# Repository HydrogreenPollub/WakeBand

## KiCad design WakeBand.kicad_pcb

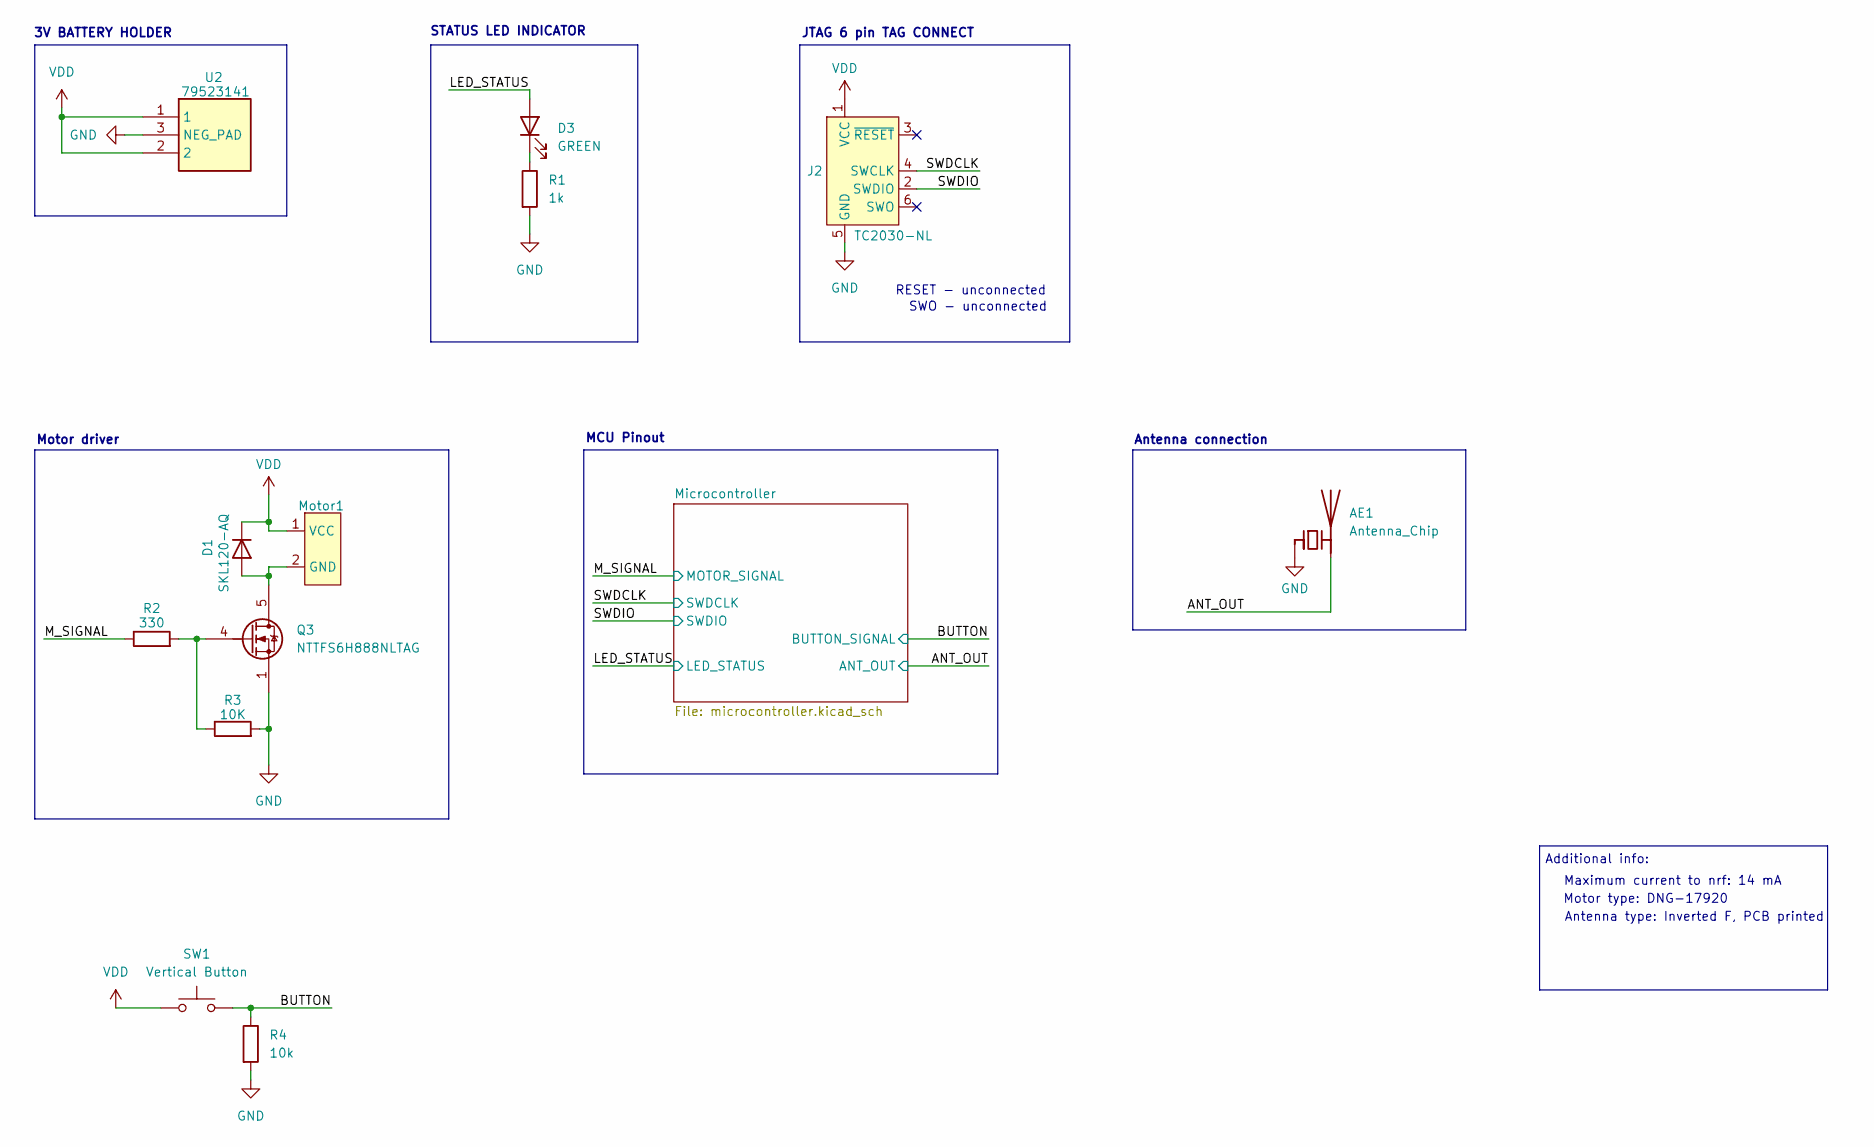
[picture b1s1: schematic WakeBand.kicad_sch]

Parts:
AE1: Antenna_Chip; ESPRESSIF_ESP32_MIFA_2.4GHz_Right
D1: SKL120-AQ; SODFL3718X170N
D3: GREEN; LED_1206_3216Metric
J2: TC2030-NL; Tag-Connect_TC2030-IDC-NL_2x03_P1.27mm_Vertical
Motor1: C_1206_3216Metric_Pad1.33x1.80mm_HandSolder
Q3: NTTFS6H888NLTAG; NRVTS560ETFS; Manufacturer_Part_Number NTTFS6H888NLTAG
R1: 1k; C_0402_1005Metric
R2: 330; C_0402_1005Metric
R3: 10K; C_0402_1005Metric
R4: 10k; R_0402_1005Metric
SW1: Vertical Button; Pushbutton from ST
U2: 79523141; Mouser Part Number 710-79523141

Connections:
/ANT_OUT: AE1.2 (PCB_Trace); also elsewhere on the board
/BUTTON: R4.1, SW1.2; also elsewhere on the board
/LED_STATUS: D3.2 (A); also elsewhere on the board
/M_SIGNAL: R2.1; also elsewhere on the board
/SWDCLK: J2.4 (SWCLK); also elsewhere on the board
/SWDIO: J2.2 (SWDIO); also elsewhere on the board
GND: AE1.1 (FEED), J2.5 (GND), Q3.1, R1.2, R3.2, R4.2, U2.3 (NEG_PAD); also elsewhere on the board
unnamed 14: D1.2 (A), Motor1.2 (GND), Q3.5; also elsewhere on the board
unnamed: D3.1 (K), R1.1
unnamed: Q3.4, R2.2, R3.1
VDD: D1.1 (K), J2.1 (VCC), Motor1.1 (VCC), SW1.1, U2.1, U2.2; also elsewhere on the board

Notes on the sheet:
Maximum current to nrf: 14 mA
Additional info:
MCU Pinout
JTAG 6 pin TAG CONNECT
SWO - unconnected
Motor type: DNG-17920
Antenna connection
STATUS LED INDICATOR
3V BATTERY HOLDER
RESET - unconnected
Motor driver
Antenna type: Inverted F, PCB printed

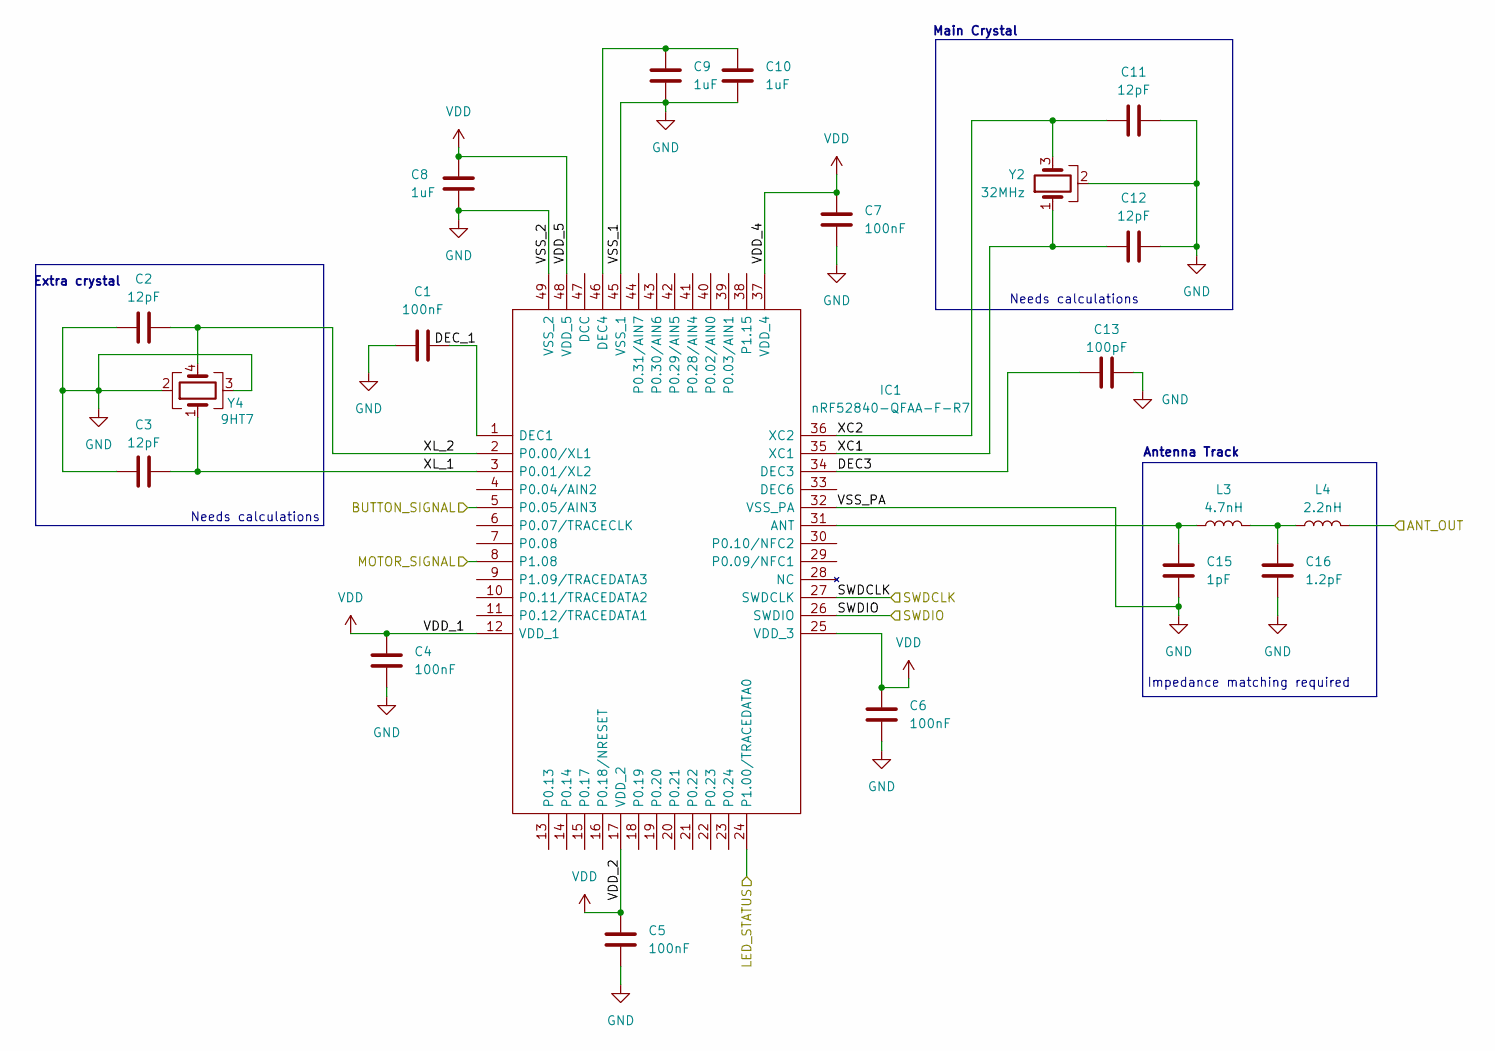
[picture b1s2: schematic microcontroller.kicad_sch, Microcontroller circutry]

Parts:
C1, C4, C5, C6, C7: 100nF; C_0402_1005Metric
C2, C3, C11, C12: 12pF; C_0402_1005Metric
C8, C9, C10: 1uF; C_0402_1005Metric
C13: 100pF; C_0402_1005Metric
C15: 1pF; C_0402_1005Metric
C16: 1.2pF; C_0402_1005Metric
IC1: nRF52840-QFAA-F-R7; QFN40P600X600X95-49N-D; Mouser Part Number 949-NRF52840QFAAF-R7
L3: 4.7nH; C_0402_1005Metric
L4: 2.2nH; C_0402_1005Metric
Y2: 32MHz; ECS320847BJTMTR
Y4: 9HT7; 9HT732768KDZFT

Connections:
/ANT_OUT: L4.2; also elsewhere on the board
/BUTTON: IC1.5 (P0.05/AIN3); also elsewhere on the board
/LED_STATUS: IC1.24 (P1.00/TRACEDATA0); also elsewhere on the board
/M_SIGNAL: IC1.8 (P1.08); also elsewhere on the board
/Microcontroller/DEC3: C13.1, IC1.34 (DEC3)
/Microcontroller/DEC_1: C1.2, IC1.1 (DEC1)
/Microcontroller/XC1: C12.1, IC1.35 (XC1), Y2.1
/Microcontroller/XC2: C11.1, IC1.36 (XC2), Y2.3
/Microcontroller/XL_1: C3.2, IC1.3 (P0.01/XL2), Y4.1
/Microcontroller/XL_2: C2.2, IC1.2 (P0.00/XL1), Y4.4
/SWDCLK: IC1.27 (SWDCLK); also elsewhere on the board
/SWDIO: IC1.26 (SWDIO); also elsewhere on the board
GND: C1.1, C2.1, C3.1, C4.2, C5.2, C6.2, C7.1, C8.1, C9.1, C10.1, C11.2, C12.2, C13.2, C15.2, C16.2, IC1.32 (VSS_PA), IC1.45 (VSS_1), IC1.49 (VSS_2), Y2.2, Y4.2, Y4.3; also elsewhere on the board
unnamed: C16.1, L3.2, L4.1
unnamed: C15.1, IC1.31 (ANT), L3.1
unnamed: C9.2, C10.2, IC1.46 (DEC4)
VDD: C4.1, C5.1, C6.1, C7.2, C8.2, IC1.12 (VDD_1), IC1.17 (VDD_2), IC1.25 (VDD_3), IC1.37 (VDD_4), IC1.48 (VDD_5); also elsewhere on the board

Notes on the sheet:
Antenna Track
Needs calculations
Main Crystal
Extra crystal
Impedance matching required

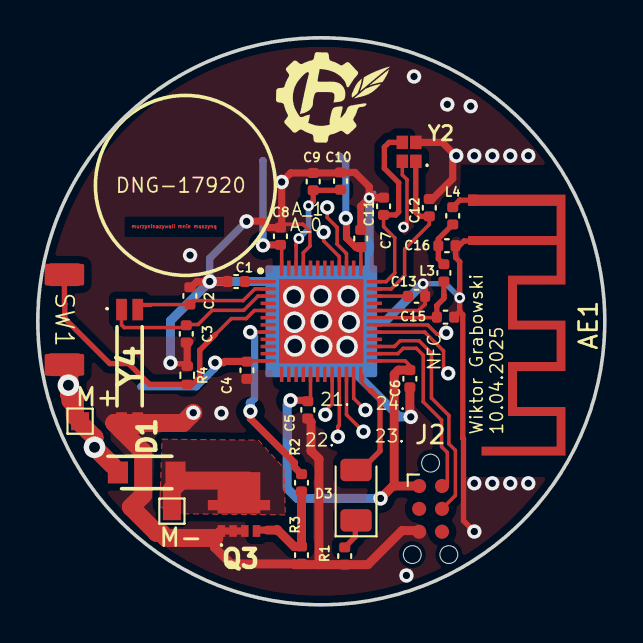
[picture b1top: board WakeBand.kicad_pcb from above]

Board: 2 copper layers, 31.5 x 31.5 mm, 33 parts (1 on the bottom side), 20 nets.

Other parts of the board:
M+: TestPoint_Pad_1.0x1.0mm
M-: TestPoint_Pad_1.0x1.0mm

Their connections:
unnamed 14: M-.1; also elsewhere on the board
VDD: M+.1; also elsewhere on the board
